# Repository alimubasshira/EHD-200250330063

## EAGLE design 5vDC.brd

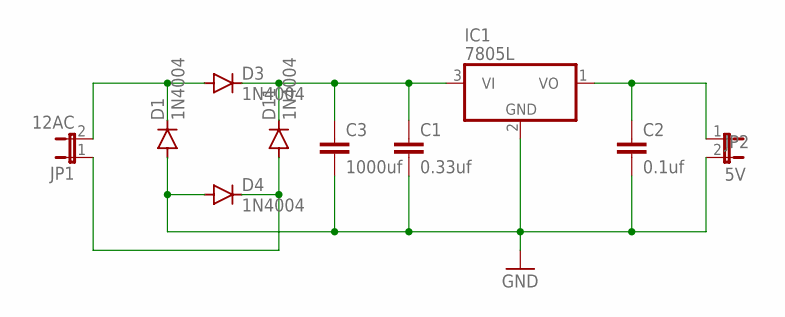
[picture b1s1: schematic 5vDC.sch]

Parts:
C1: 0.33uf; C2.5-3
C2: 0.1uf; C2.5-3
C3: 1000uf; C2.5-3
D1, D3, D4, D11: 1N4004; DO41-10
IC1: 7805L; TO92
JP1: 12AC; JP1
JP2: 5V; JP1

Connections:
GND: C1.2, C2.2, C3.2, D1.A, D4.A, IC1.2 (GND), JP2.2
unnamed: D1.C, D3.A, JP1.2
unnamed: C1.1, C3.1, D3.C, D11.C, IC1.3 (VI)
unnamed: C2.1, IC1.1 (VO), JP2.1
unnamed: D4.C, D11.A, JP1.1

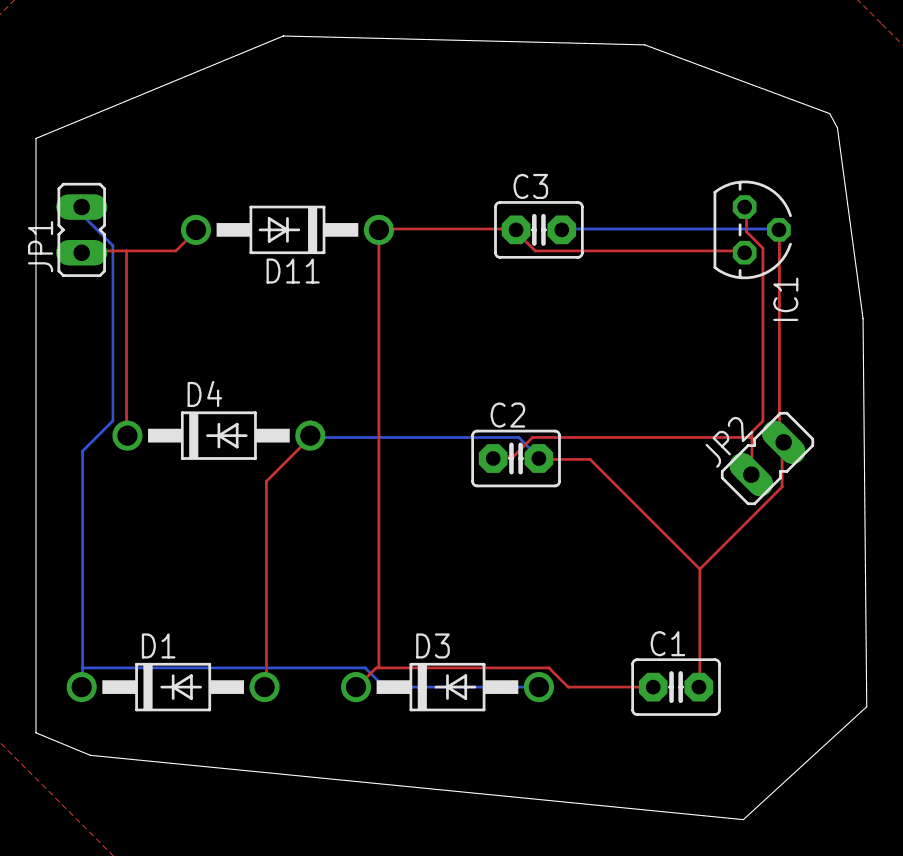
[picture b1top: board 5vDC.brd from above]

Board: 2 copper layers, 46.2 x 43.5 mm, 10 parts (0 on the bottom side), 5 nets.
